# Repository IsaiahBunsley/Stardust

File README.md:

# Stardust
Harmonic gear driven equatorial mount for astrophotography.

GOALS:
 - Achieve sub arcsecond prescision
 - Make a sleek and nice-to-view body assembly
 - Use as few pre-made assemblies as possible
 - Ample wieght capacity ( >10 lbs, ideally >20 lbs )
 - Ease of use/control using pre-developed software such as PHD2, OnStep, etc...
 - Design a PCB to house stepper controllers, microcrontroller, WiFi, etc..
 - Efficient homing process
 - Create a product that is not only good-looking but easy to use and enjoy

NOTES:
V1 Is way to large and clunky

Using a 100:1 harmonic and a ~3.33:1 pulley system we can achieve sub arcsecond tracking using 256 microstepping and approx 20 arcsecond tracking with no microstepping. UPDATE: Using a 0.9deg stepper 10 arcsecond (per step)
can be had. A 0.9deg stepper with 1/16 microstepping will give us 0.6 arcseconds per step. This will have to be used to meet design requiremetns as well as to avoid microstepping as it can lead to error.

M3 bolts were used on bolting the body together. If this does not prove to be rigid enough more bolts can be added or a redesign including angle brackets will be needed.

Clearances with the stepper motors are extremely tight. If NEMA 17 motors will not work it would be OK to swap the DEC axis for a smaller NEMA 14 stepper.

Product IDs for the gears are given but expensive. If suitable replacements with similar specs can be found it would be OK to swap. Same with belts. The only issue would be lack of 
quality control from other sources (Amazon...). Cheaping out on a $20 belt would introduce backlash and tracking errors to the ~$1000 harmonic drives.

The angle brackets used to mount the steppers are called out as 6061 alum alloy but could possibly be 3d printed or bought from Mcmaster Carr if a similar design was found.

A redesign of the tangent mount is needed. This tangent mount is made by William Optics and could be fitted into the design for $250: https://williamoptics.com/products/wo-vixen-style-latitude-base-mount?srsltid=AfmBOoq2dK0res2H1lodv_DhOAtTPYLHiSqc_pLKRGRtTDOESbJT08JW

After looking through the new AM5N's product specs the following seems true:
reduction ratio: 300:1 
         This means that they are using a 100:1 HD paired with a 3:1 belt. With this setup they are claiming a arcsec/step of 0.17. This means that they are using stepper microstepping of 1/64 (0.9 / 300 / 64 = deg -> 0.1687 arcseconds) (also assuming 0.9deg steppers).
There is also a claimed "high payload" mode. I believe that this "mode" simply changes the microstepping value to something more reasonable such as 1/16. This will increase the availiable current per step and thus give more reliable tracking (less periodic error) where more current per step is needed (higher payloads).

DESIGN IDEAS:
For implementing a homing process - Use a arm that mounts to the main axis (axe-eees) that goes down the length of the HD and will pass over some sort of magnetic sensor or inductive position
sensor. This will allow the motors to spin the HD until a sensor detects an object meaning the output shaft of the HD is in the correct location.

Add an encoder and brake to the stepper shaft. 

Allow for EQ mode OR an alt/az mode (by removing the tangent assembly).

INSPIRATION:
Alkaid by JZ - https://github.com/alanzjl/AlkaidMount
ZWO AM5 - https://www.highpointscientific.com/zwo-am5n-harmonic-drive-equatorial-mount-with-tripod
William Optics Latitude Base - https://williamoptics.com/products/wo-vixen-style-latitude-base-mount?srsltid=AfmBOoq2dK0res2H1lodv_DhOAtTPYLHiSqc_pLKRGRtTDOESbJT08JW

0.9 Stepper - https://www.moonsindustries.com/p/nema-17-high-precision-hybrid-stepper-motors/ms17ha4p4040-000004611110015909
ONSTEP      - https://onstep.groups.io/g/main/wiki/4414

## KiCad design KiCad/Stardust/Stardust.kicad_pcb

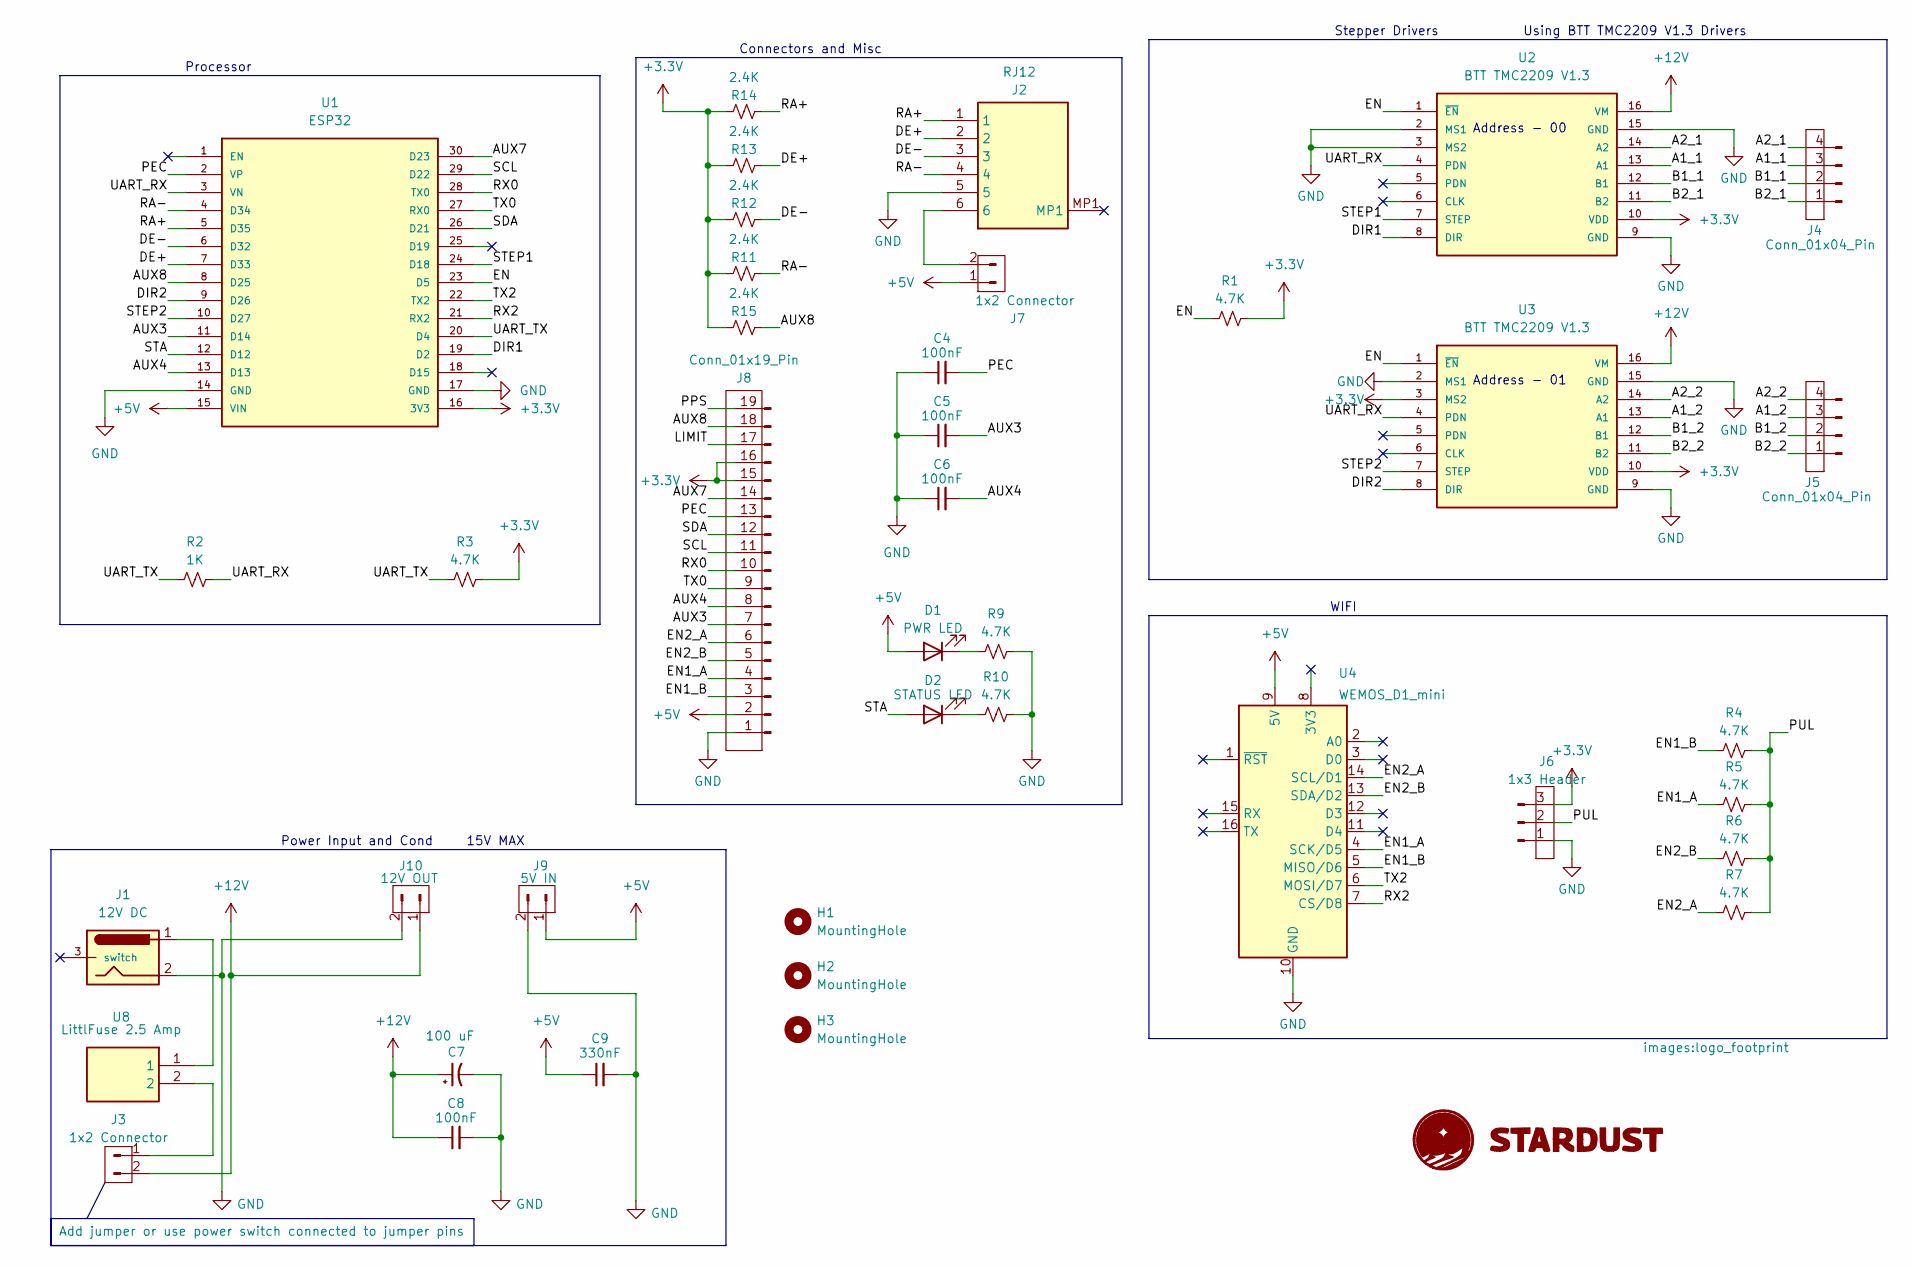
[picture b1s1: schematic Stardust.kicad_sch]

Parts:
C4, C5, C6, C8: 100nF; C_0805_2012Metric_Pad1.18x1.45mm_HandSolder; Mouser PN 581-KAM21BR71H104JT
C7: 100 uF; 100uFElectrolyticCap_CAPAE830X1080N; Mouser PN 647-GXC1V101MCQ1GS
C9: 330nF; C_1206_3216Metric_Pad1.33x1.80mm_HandSolder; Mouser PN 581-KAM31NR81H334KU
D1: PWR LED; LED_0603_1608Metric_Pad1.05x0.95mm_HandSolder
D2: STATUS LED; LED_0603_1608Metric_Pad1.05x0.95mm_HandSolder
G1: LOGO; logo_footprint
H1, H2, H3: MountingHole; MountingHole_3.2mm_M3
J1: 12V DC; DC_PowerConn_694108402002
J2: RJ12; RJ12_855135114; Mouser Part Number 538-85513-5002
J3, J7: 1x2 Connector; PinHeader_1x02_P2.54mm_Vertical
J4, J5: Conn_01x04_Pin; PinHeader_1x04_P2.54mm_Vertical
J6: 1x3 Header; PinHeader_1x03_P2.54mm_Vertical
J8: Conn_01x19_Pin; PinHeader_1x19_P2.54mm_Vertical
J9: 5V IN; PinHeader_1x02_P2.54mm_Vertical
J10: 12V OUT; PinHeader_1x02_P2.54mm_Vertical
R1, R3, R4, R5, R6, R7, R9, R10: 4.7K; R_0805_2012Metric_Pad1.20x1.40mm_HandSolder
R2: 1K; R_0805_2012Metric_Pad1.20x1.40mm_HandSolder
R11, R12, R13, R14, R15: 2.4K; R_0805_2012Metric_Pad1.20x1.40mm_HandSolder
U1: ESP32; MODULE_ESP32-DEVKITC
U2, U3: BTT TMC2209 V1.3; MODULE_TMC2209_SILENTSTEPSTICK
U4: WEMOS_D1_mini; WEMOS_D1_mini_light
U8: LittlFuse 2.5 Amp; FuseHolder_RHDR2W53P0X508_1X2; Mouser Part Number 576-56200001009

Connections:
+3.3V: J6.3, J8.15, J8.16, R1.2, R3.2, R11.2, R12.2, R13.2, R14.2, R15.2, U1.16 (3V3), U2.10 (VDD), U3.3 (MS2), U3.10 (VDD)
+5V: C9.1, D1.2 (A), J7.1, J8.2, J9.1, U1.15 (VIN), U4.9 (5V)
+12V: C7.1, C8.1, J3.2, J10.1, U2.16 (VM), U3.16 (VM)
/A1_1: J4.3, U2.13 (A1)
/A1_2: J5.3, U3.13 (A1)
/A2_1: J4.4, U2.14 (A2)
/A2_2: J5.4, U3.14 (A2)
/AUX3: C5.2, J8.7, U1.11 (D14)
/AUX4: C6.2, J8.8, U1.13 (D13)
/AUX7: J8.14, U1.30 (D23)
/AUX8: J8.18, R15.1, U1.8 (D25)
/B1_1: J4.2, U2.12 (B1)
/B1_2: J5.2, U3.12 (B1)
/B2_1: J4.1, U2.11 (B2)
/B2_2: J5.1, U3.11 (B2)
/DE+: J2.2, R13.1, U1.7 (D33)
/DE-: J2.3, R12.1, U1.6 (D32)
/DIR1: U1.19 (D2), U2.8 (DIR)
/DIR2: U1.9 (D26), U3.8 (DIR)
/EN: R1.1, U1.23 (D5), U2.1 (~EN), U3.1 (~EN)
/EN1_A: J8.4, R5.1, U4.4 (SCK/D5)
/EN1_B: J8.3, R4.1, U4.5 (MISO/D6)
/EN2_A: J8.6, R7.1, U4.14 (SCL/D1)
/EN2_B: J8.5, R6.1, U4.13 (SDA/D2)
/LIMIT: J8.17
/PEC: C4.2, J8.13, U1.2 (VP)
/PPS: J8.19
/PUL: J6.2, R4.2, R5.2, R6.2, R7.2
/RA+: J2.1, R14.1, U1.5 (D35)
/RA-: J2.4, R11.1, U1.4 (D34)
/RX0: J8.10, U1.28 (TX0)
/RX2: U1.21 (RX2), U4.7 (CS/D8)
/SCL: J8.11, U1.29 (D22)
/SDA: J8.12, U1.26 (D21)
/STA: D2.2 (A), U1.12 (D12)
/STEP1: U1.24 (D18), U2.7 (STEP)
/STEP2: U1.10 (D27), U3.7 (STEP)
/TX0: J8.9, U1.27 (RX0)
/TX2: U1.22 (TX2), U4.6 (MOSI/D7)
/UART_RX: R2.2, U1.3 (VN), U2.4 (PDN), U3.4 (PDN)
/UART_TX: R2.1, R3.1, U1.20 (D4)
GND: C4.1, C5.1, C6.1, C7.2, C8.2, C9.2, J1.2, J2.5, J6.1, J8.1, J9.2, J10.2, R9.2, R10.2, U1.14 (GND), U1.17 (GND), U2.2 (MS1), U2.3 (MS2), U2.9 (GND), U2.15 (GND), U3.2 (MS1), U3.9 (GND), U3.15 (GND), U4.10 (GND)
unnamed: D1.1 (K), R9.1
unnamed: D2.1 (K), R10.1
unnamed: J1.1, U8.1
unnamed: J3.1, U8.2
unnamed: J2.6, J7.2

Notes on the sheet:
Processor
Connectors and Misc
Using BTT TMC2209 V1.3 Drivers
WIFI
15V MAX
Stepper Drivers
Address - 01
Power Input and Cond
Address - 00

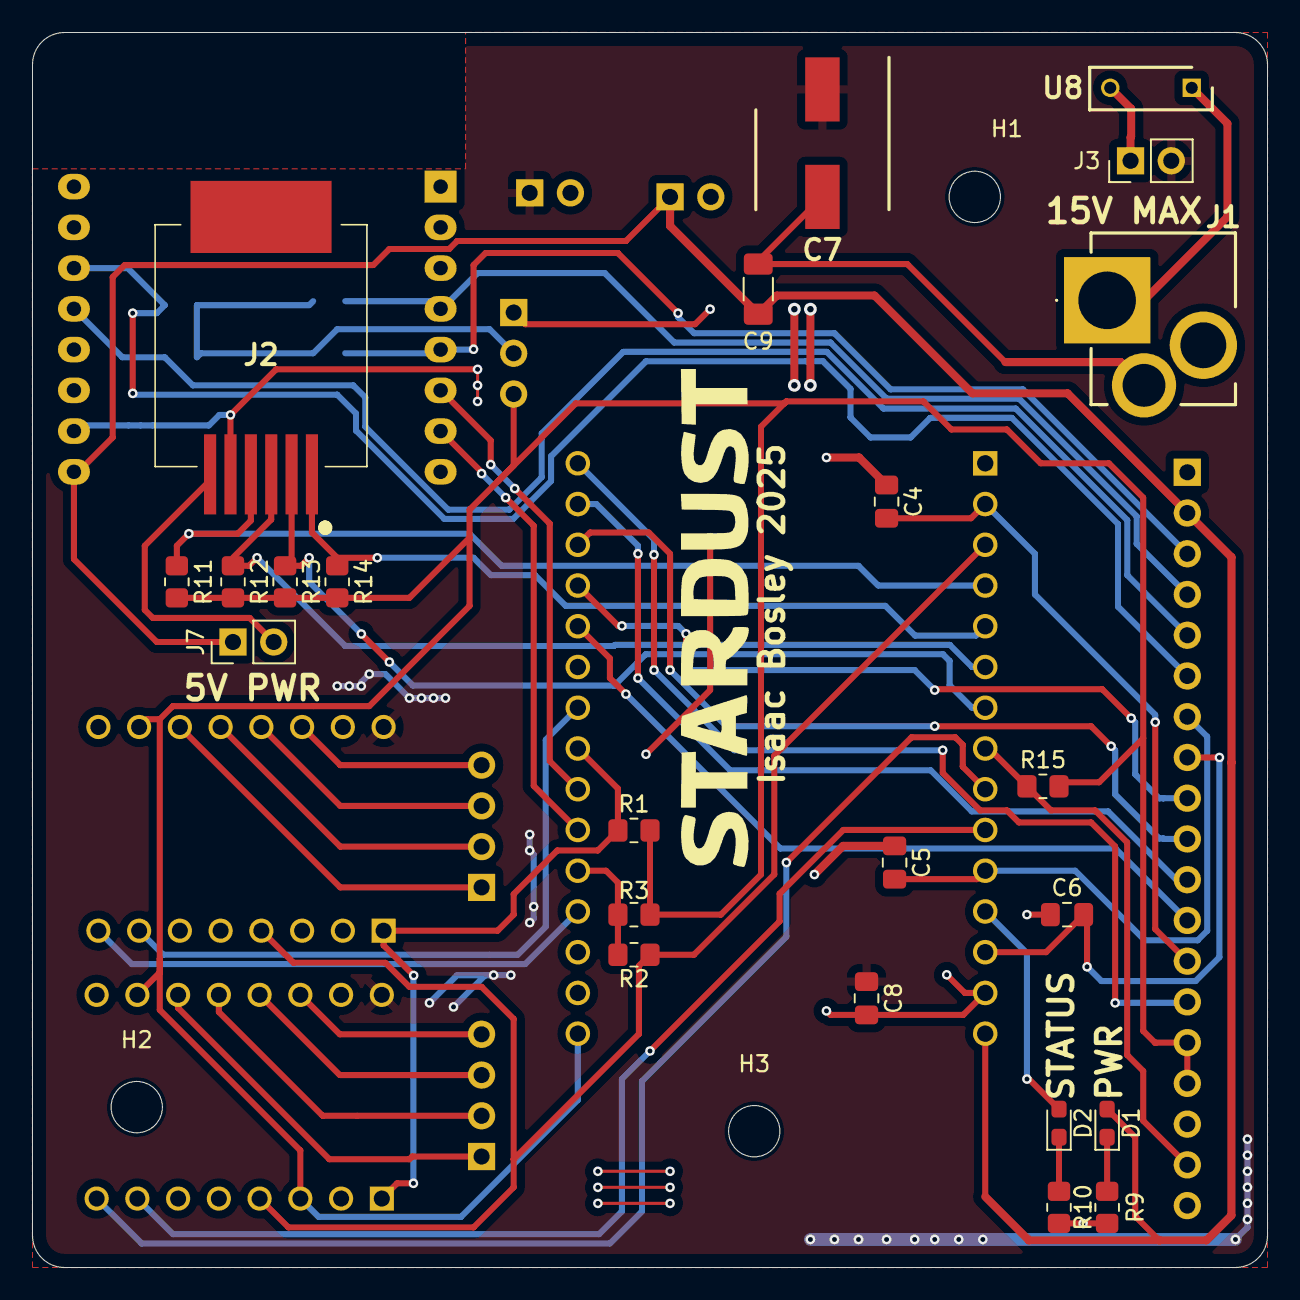
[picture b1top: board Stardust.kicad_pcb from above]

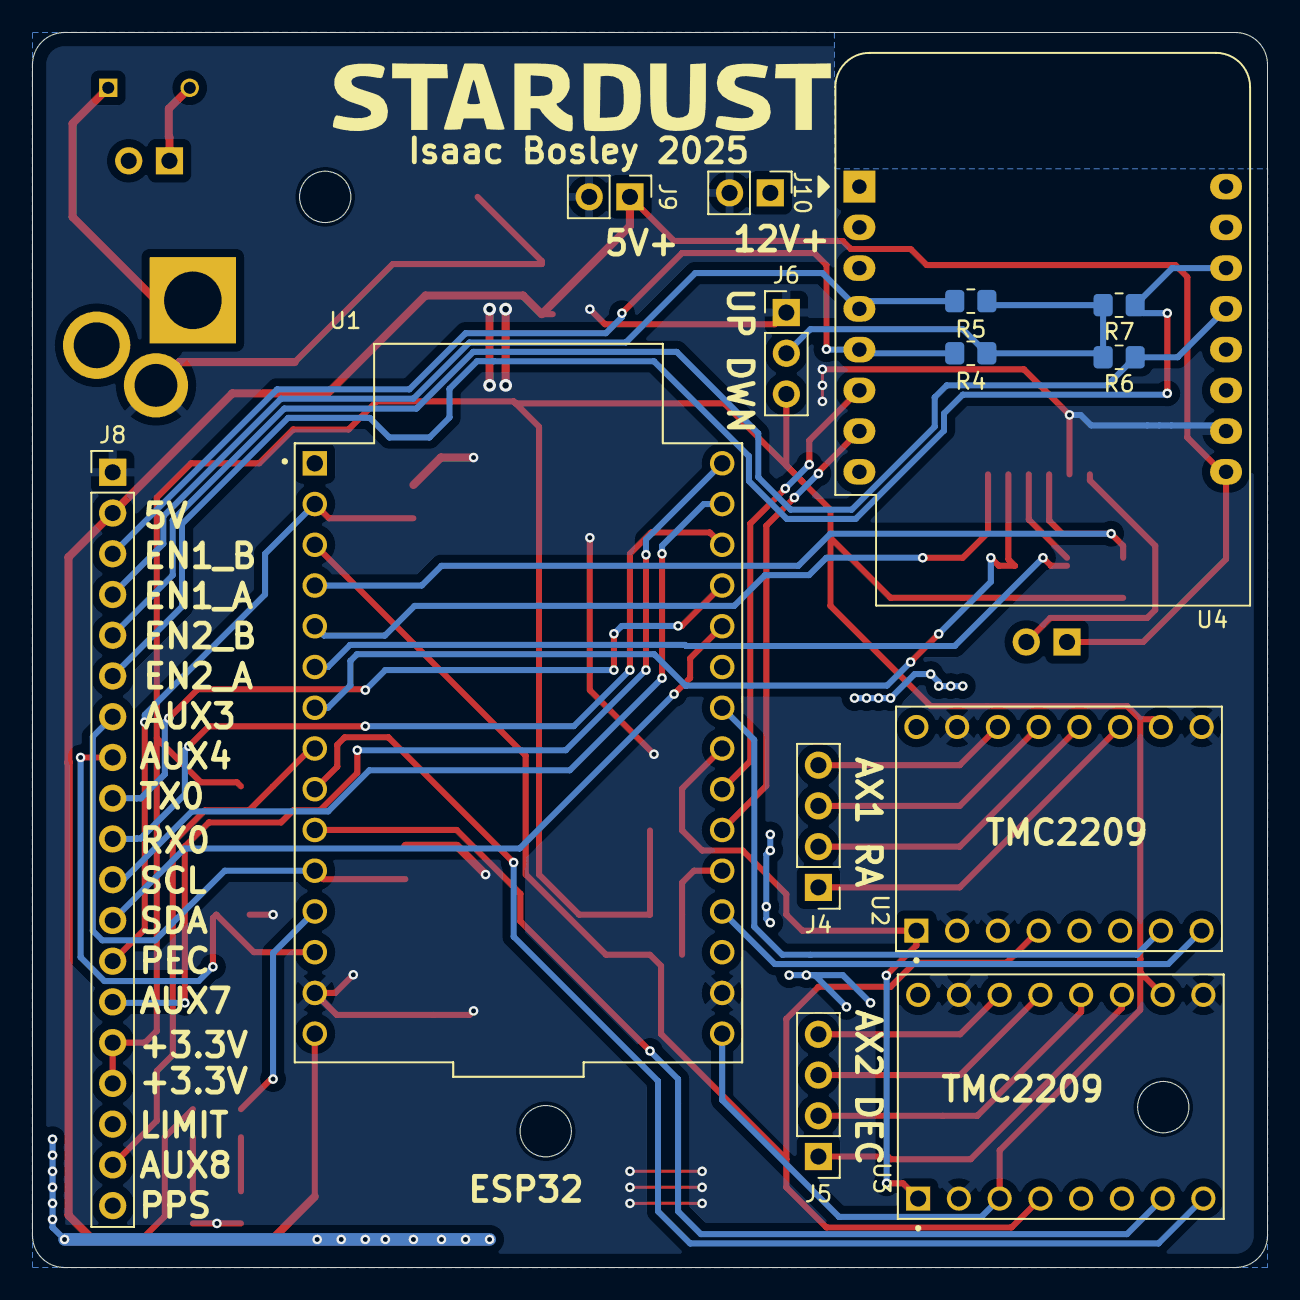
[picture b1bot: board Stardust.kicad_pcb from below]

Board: 2 copper layers, 77.0 x 77.0 mm, 42 parts (15 on the bottom side), 45 nets.

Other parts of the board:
G1#2: LOGO; logo_footprint

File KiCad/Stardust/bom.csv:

"Id";"Designator";"Footprint";"Quantity";"Designation";"Supplier and ref";
1;"C6,C5,C8,C4";"C_2220_5750Metric_Pad1.97x5.40mm_HandSolder";4;"100nF";;;
2;"R1,R3,R9,R10,R6,R5,R4,R7";"R_0805_2012Metric_Pad1.20x1.40mm_HandSolder";8;"4.7K";;;
3;"D2";"LED_0603_1608Metric_Pad1.05x0.95mm_HandSolder";1;"STATUS LED";;;
4;"J7,J3";"PinHeader_1x02_P2.54mm_Vertical";2;"1x2 Connector";;;
5;"J2";"RJ12_855135114";1;"RJ12";;;
6;"R14,R15,R13,R12,R11";"R_0805_2012Metric_Pad1.20x1.40mm_HandSolder";5;"2.4K";;;
7;"U8";"FuseHolder_RHDR2W53P0X508_1X2";1;"LittlFuse 2.5 Amp";;;
8;"G1,G1";"logo_footprint";2;"LOGO";;;
9;"C7";"100uFElectrolyticCap_CAPAE830X1080N";1;"100 uF";;;
10;"U7";"5VREG_SOT230P700X180-4N";1;"Regulator - 5V 1A";;;
11;"C2,C1";"10uFElectrolyticCap_CAPAE660X550N";2;"10 uF";;;
12;"D1";"LED_0603_1608Metric_Pad1.05x0.95mm_HandSolder";1;"PWR LED";;;
13;"C3";"C_0603_1608Metric_Pad1.08x0.95mm_HandSolder";1;"10uF";;;
14;"C9";"C_1206_3216Metric_Pad1.33x1.80mm_HandSolder";1;"330nF";;;
15;"R2";"R_0805_2012Metric_Pad1.20x1.40mm_HandSolder";1;"1K";;;
16;"J1";"DC_PowerConn_694108402002";1;"12V DC";;;
17;"U2,U3";"MODULE_TMC2209_SILENTSTEPSTICK";2;"BTT TMC2209 V1.3";;;
18;"U1";"MODULE_ESP32-DEVKITC";1;"ESP32";;;
19;"J5,J4";"PinHeader_1x04_P2.54mm_Vertical";2;"Conn_01x04_Pin";;;
20;"J6";"PinHeader_1x03_P2.54mm_Vertical";1;"1x3 Header";;;
21;"J8";"PinHeader_1x19_P2.54mm_Vertical";1;"Conn_01x19_Pin";;;
22;"U4";"WEMOS_D1_mini_light";1;"WEMOS_D1_mini";;;

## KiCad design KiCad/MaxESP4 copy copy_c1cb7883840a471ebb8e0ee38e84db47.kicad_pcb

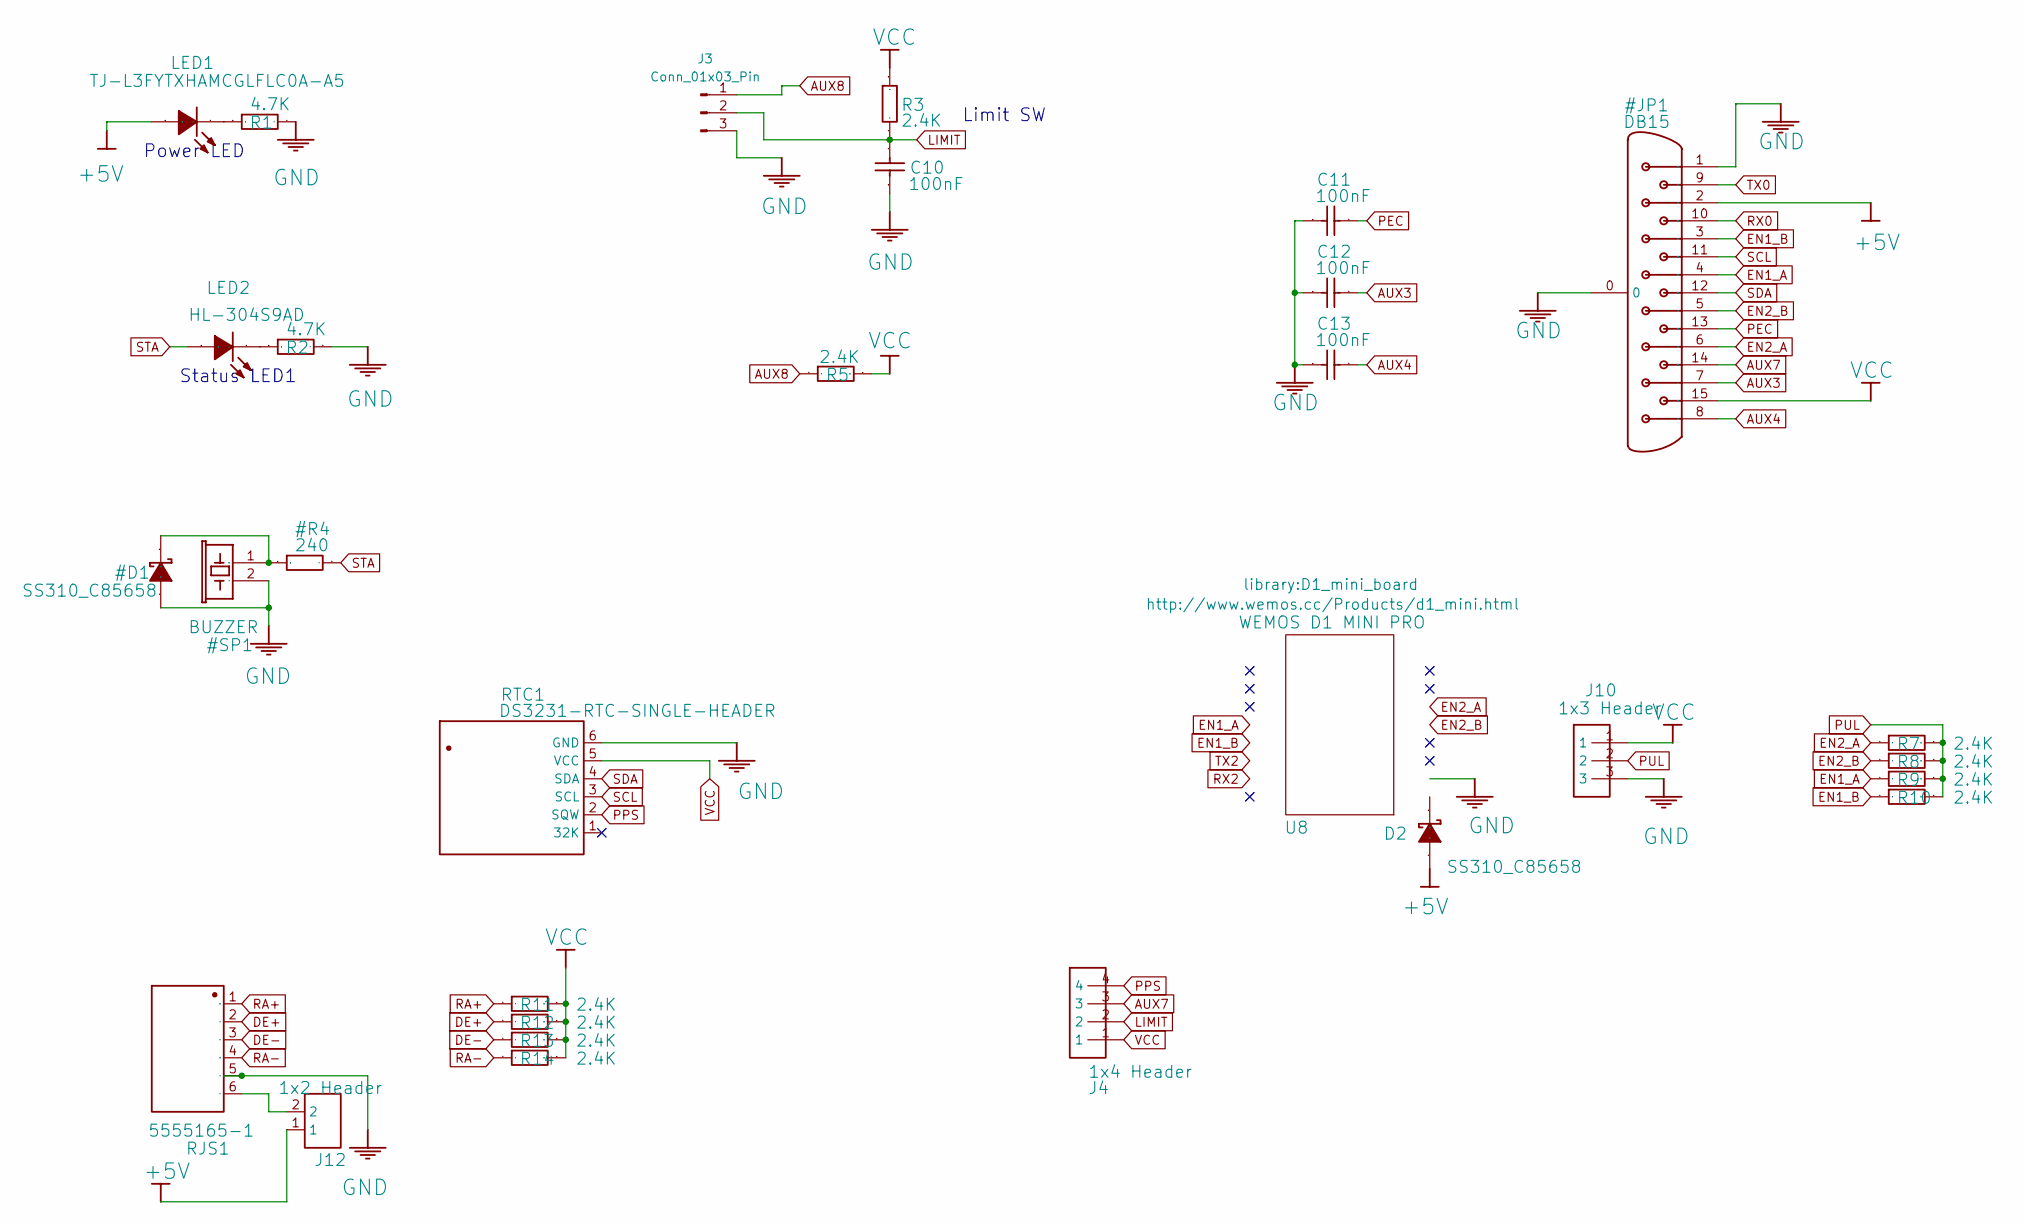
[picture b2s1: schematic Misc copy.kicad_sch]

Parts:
C10, C11, C12, C13: 100nF; 0.1uF_CAPC2012X94N
D2: SS310_C85658; Schottky_SODFL5336X130N
J3: Conn_01x03_Pin; PinHeader_1x03_P2.54mm_Vertical
J4: 1x4 Header; PinHeader_1x04_P2.54mm_Vertical
J10: 1x3 Header; PinHeader_1x03_P2.54mm_Vertical
J12: 1x2 Header; PinHeader_1x02_P2.54mm_Vertical
LED1: TJ-L3FYTXHAMCGLFLC0A-A5; LED_AA1608LZGSK295V
LED2: HL-304S9AD; LED_AA1608LZGSK295V
R1, R2: 4.7K; 4.7K_Resistor_ERA8P
R3, R5, R7, R8, R9, R10, R11, R12, R13, R14: 2.4K; 2.4K_Resistor_ERJUP6
RJS1: 5555165-1
RTC1: DS3231-RTC-SINGLE-HEADER
U8: WEMOS D1 MINI PRO; D1_mini_board

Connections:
AUX8: J3.1, R5.2; also elsewhere on the board
DE+: R12.2, RJS1.2; also elsewhere on the board
DE-: R13.2, RJS1.3; also elsewhere on the board
LIMIT: C10.2, J3.2, J4.2, R3.2
unnamed: D2.1 (K), U8.1 (5V)
unnamed: J12.2, RJS1.6
unnamed: LED1.2 (C), R1.1
unnamed: LED2.2 (C), R2.1
PPS: J4.4, RTC1.2 (SQW)
PUL: J10.2, R7.1, R8.1, R9.1, R10.1
RA+: R11.2, RJS1.1; also elsewhere on the board
RA-: R14.2, RJS1.4; also elsewhere on the board
RX2: U8.15 (D8); also elsewhere on the board
TX2: U8.14 (D7); also elsewhere on the board

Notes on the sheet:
Limit SW
Status LED1
Power LED

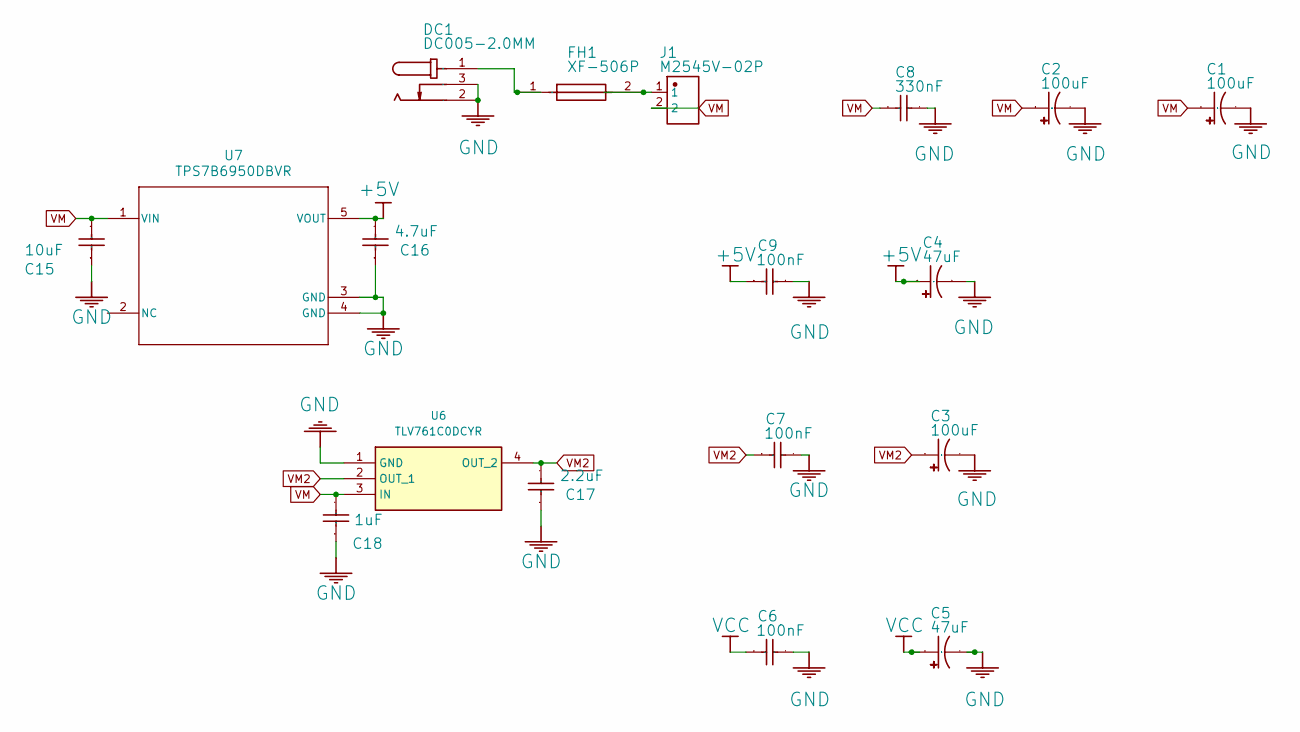
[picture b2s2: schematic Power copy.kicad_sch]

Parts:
C1, C2, C3: 100uF; 47uF_100uF_Capacitor_CAPAE830X1080N
C4, C5: 47uF; 47uF_100uF_Capacitor_CAPAE830X1080N
C6, C7, C9: 100nF; 0.1uF_CAPC2012X94N
C8: 330nF; 0.33uF_Capacitor_CAPC3216X127N
C15: 10uF; 0.1uF_CAPC2012X94N
C16: 4.7uF; 0.1uF_CAPC2012X94N
C17: 2.2uF; 0.1uF_CAPC2012X94N
C18: 1uF; 0.1uF_CAPC2012X94N
DC1: DC005-2.0MM; DC_PowerConn_694108402002
FH1: XF-506P; FuseHolder_RHDR2W53P0X508_1X2_765X255X455P
J1: M2545V-02P; PinHeader_1x02_P2.54mm_Vertical
U6: TLV761C0DCYR; SOT230P700X180-4N; Mouser Part Number 595-TLV761C0DCYR
U7: TPS7B6950DBVR; DBV0005A_N

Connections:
unnamed: DC1.1, FH1.1
unnamed: FH1.2, J1.1
VM: C1.1, C2.1, C8.1, C15.2, C18.2, J1.2, U6.3 (IN), U7.1 (VIN); also elsewhere on the board

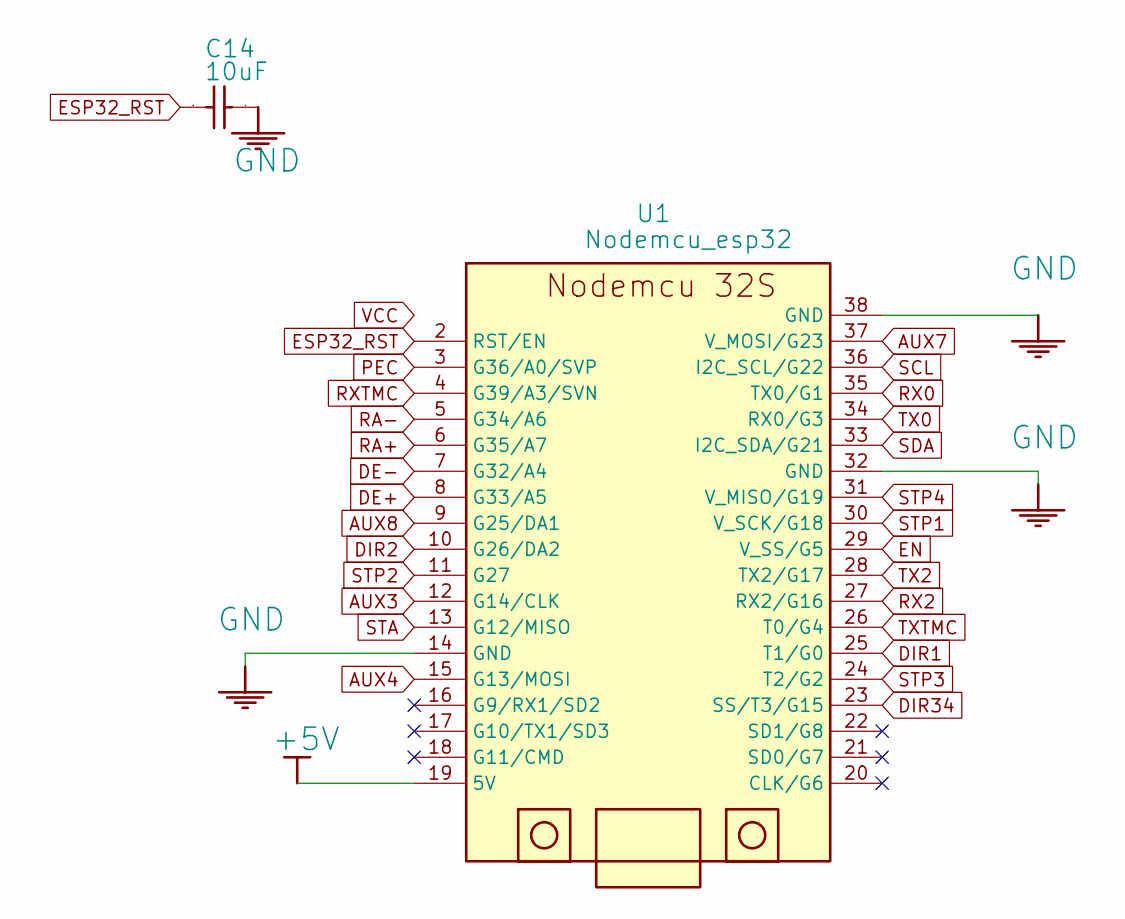
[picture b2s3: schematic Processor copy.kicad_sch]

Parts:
C14: 10uF; 10uF_Capacitor_CAPC3216X190N
U1: Nodemcu_esp32; MODULE_ESP32-DEVKITC

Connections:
AUX8: U1.9 (G25/DA1); also elsewhere on the board
DE+: U1.8 (G33/A5); also elsewhere on the board
DE-: U1.7 (G32/A4); also elsewhere on the board
DIR1: U1.25 (T1/G0); also elsewhere on the board
DIR2: U1.10 (G26/DA2); also elsewhere on the board
DIR34: U1.23 (SS/T3/G15)
ESP32_RST: C14.1, U1.2 (RST/EN)
RA+: U1.6 (G35/A7); also elsewhere on the board
RA-: U1.5 (G34/A6); also elsewhere on the board
RX0: U1.35 (TX0/G1)
RX2: U1.27 (RX2/G16); also elsewhere on the board
STP1: U1.30 (V_SCK/G18); also elsewhere on the board
STP2: U1.11 (G27); also elsewhere on the board
STP3: U1.24 (T2/G2)
STP4: U1.31 (V_MISO/G19)
TX0: U1.34 (RX0/G3)
TX2: U1.28 (TX2/G17); also elsewhere on the board
TXTMC: U1.26 (T0/G4); also elsewhere on the board

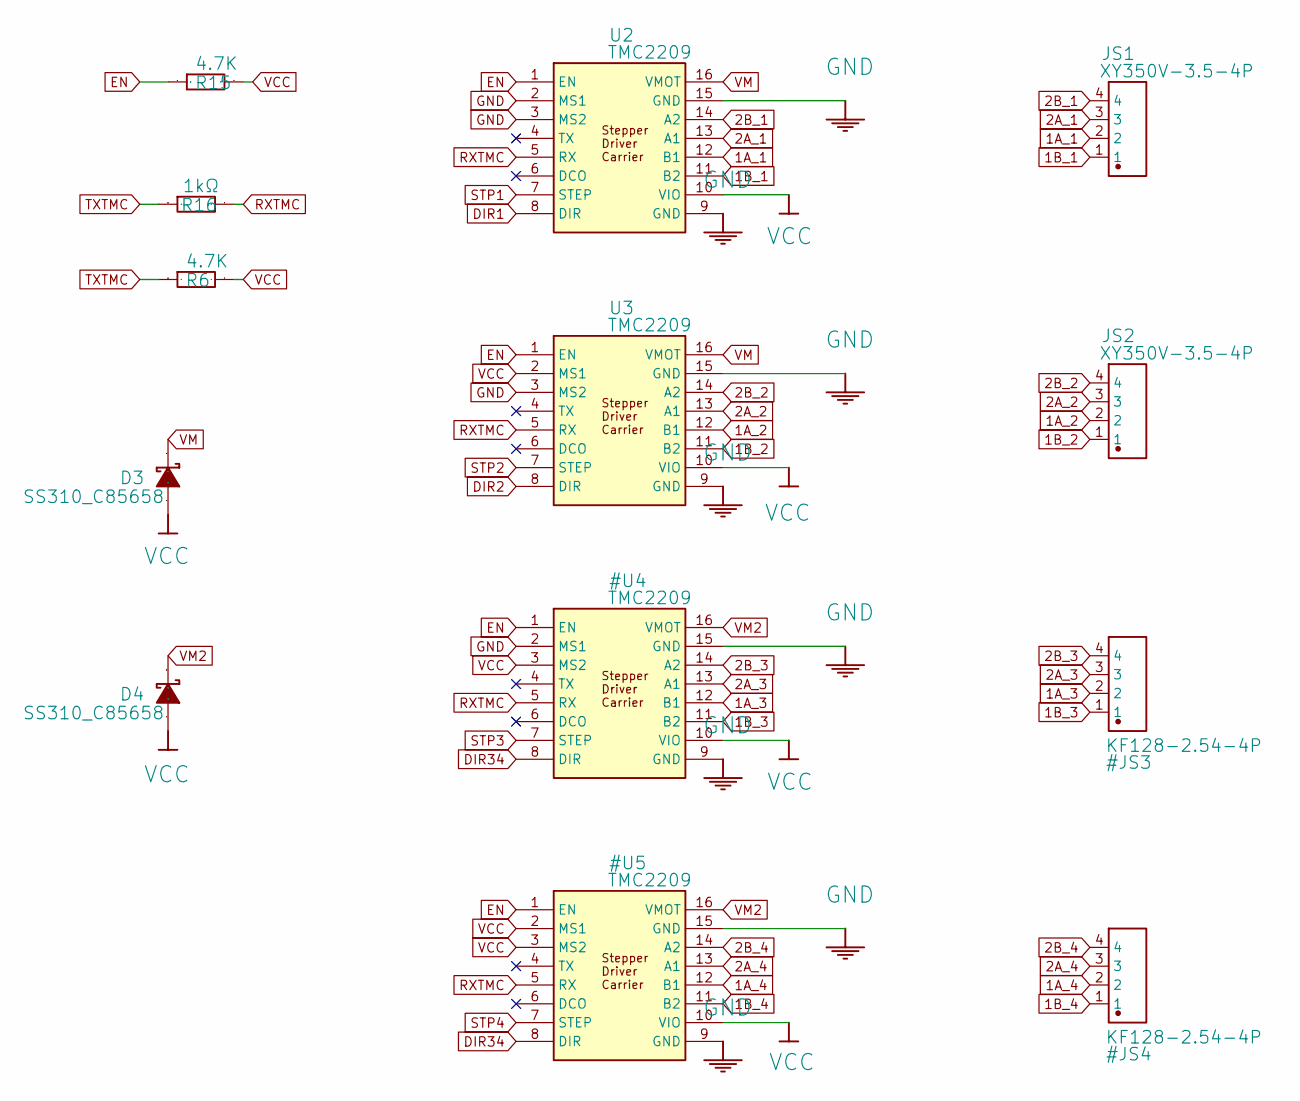
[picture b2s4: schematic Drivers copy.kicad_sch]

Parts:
D3, D4: SS310_C85658; Schottky_SODFL5336X130N
JS1, JS2: XY350V-3.5-4P; PinHeader_1x04_P2.54mm_Vertical
R6, R15: 4.7K; 4.7K_Resistor_ERA8P
R16: 1kΩ; 1k_Resistor_RESC3216X70N
U2, U3: TMC2209; MODULE_TMC2209_SILENTSTEPSTICK

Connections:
1A_1: JS1.2, U2.12 (B1)
1A_2: JS2.2, U3.12 (B1)
1B_1: JS1.1, U2.11 (B2)
1B_2: JS2.1, U3.11 (B2)
2A_1: JS1.3, U2.13 (A1)
2A_2: JS2.3, U3.13 (A1)
2B_1: JS1.4, U2.14 (A2)
2B_2: JS2.4, U3.14 (A2)
DIR1: U2.8 (DIR); also elsewhere on the board
DIR2: U3.8 (DIR); also elsewhere on the board
STP1: U2.7 (STEP); also elsewhere on the board
STP2: U3.7 (STEP); also elsewhere on the board
TXTMC: R6.1, R16.1; also elsewhere on the board
VM: D3.1 (K), U2.16 (VMOT), U3.16 (VMOT); also elsewhere on the board

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
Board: 2 copper layers, 54 parts (0 on the bottom side), 47 nets, no tracks yet.

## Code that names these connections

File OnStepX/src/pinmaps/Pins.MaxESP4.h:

// -------------------------------------------------------------------------------------------------
// Pin map for OnStep MaxESP4 (ESP32S)
#pragma once

#if defined(ESP32)

// Serial0: RX Pin GPIO3, TX Pin GPIO1 (to USB serial adapter)
// Serial1: RX1 Pin GPIO10, TX1 Pin GPIO9 (on SPI Flash pins, must be moved to be used)
// Serial2: RX2 Pin GPIO16, TX2 Pin GPIO17

#if SERIAL_A_BAUD_DEFAULT != OFF
  #define SERIAL_A              Serial
#endif
#if SERIAL_B_BAUD_DEFAULT != OFF
  #define SERIAL_B              Serial2
#endif

// Use the following settings for any TMC UART driver (TMC2209) that may be present
#if defined(STEP_DIR_TMC_UART_PRESENT) || defined(SERVO_TMC2209_PRESENT)
  #define SERIAL_TMC_HARDWARE_UART
  #define SERIAL_TMC            Serial1          // Use a single hardware serial port to up to four drivers
  #define SERIAL_TMC_BAUD       460800           // Baud rate
  #define SERIAL_TMC_RX         39               // Recieving data
  #define SERIAL_TMC_TX         4                // Transmit data
  #define SERIAL_TMC_ADDRESS_MAP(x) ((x==1)?2 : x) // Axis1(0) is 0, Axis2(1) is 1, Axis3(2) is 2, Axis4(3) is 3, Axis5(4) is 2
#endif

// Specify the ESP32 I2C pins
#define I2C_SDA_PIN             21
#define I2C_SCL_PIN             22

// The multi-purpose pins (Aux3..Aux8 can be analog pwm/dac if supported)
#define AUX2_PIN                39               // M3 pin TMC UART RX
#define AUX3_PIN                14               // Home SW for Axis1
#define AUX4_PIN                13               // Home SW for Axis2
#define AUX5_PIN                1                // TX0 main USB, etc.
#define AUX6_PIN                3                // RX0 main USB, etc.
#define AUX7_PIN                23               // Limit SW, PPS, etc.
#define AUX8_PIN                25               // 1-Wire, Status LED, Reticle LED, Tone, etc.

// Misc. pins
#ifndef ONE_WIRE_PIN
  #define ONE_WIRE_PIN          AUX8_PIN         // Default Pin for OneWire bus
#endif

// The PEC index sense is a logic level input, resets the PEC index on rising edge then waits for 60 seconds before allowing another reset
#ifndef PEC_SENSE_PIN
  #define PEC_SENSE_PIN         36               // [input only 36] PEC Sense, analog (A0) or digital (GPIO36)
#endif

// The status LED w/ 4.7k resistor in series to limit the current to the LED
#ifdef STATUS_LED_ON_STATE
  #undef STATUS_LED_ON_STATE
#endif
#define STATUS_LED_ON_STATE HIGH
#ifndef STATUS_LED_PIN
  #define STATUS_LED_PIN        12               // Default LED Anode (+)
#endif
#ifdef MOUNT_LED_ON_STATE
  #undef MOUNT_LED_ON_STATE
#endif
#define MOUNT_LED_ON_STATE      HIGH
#define MOUNT_LED_PIN           STATUS_LED_PIN   // Default LED Anode (+)
#ifndef RETICLE_LED_PIN
  #define RETICLE_LED_PIN       AUX8_PIN         // Default LED Cathode (-)
#endif

// For a piezo buzzer
#ifndef STATUS_BUZZER_PIN
  #define STATUS_BUZZER_PIN     12               // [must be low at boot 12] Tone
#endif

// The PPS pin is a 3.3V logic input, OnStep measures time between rising edges and adjusts the internal sidereal clock frequency
#ifndef PPS_SENSE_PIN
  #define PPS_SENSE_PIN         AUX7_PIN         // PPS time source, GPS for example
#endif

// The limit switch sense is a logic level input normally pull high (2k resistor,) shorted to ground it stops gotos/tracking
#ifndef LIMIT_SENSE_PIN
  #define LIMIT_SENSE_PIN       AUX7_PIN
#endif

#define SHARED_DIRECTION_PINS                    // Hint that the direction pins are shared
#define SHARED_ENABLE_PIN       5                // Hint that the enable pins are shared

// Axis1 RA/Azm step/dir driver
#define AXIS1_ENABLE_PIN        SHARED           // Enable pin control
#define AXIS1_M0_PIN            OFF              // hardwired for TMC UART address 0
#define AXIS1_M1_PIN            OFF              // hardwired for TMC UART address 0
#define AXIS1_M2_PIN            OFF              // UART TX
#define AXIS1_M3_PIN            OFF              // UART RX
#define AXIS1_STEP_PIN          18
#define AXIS1_DIR_PIN           2                // [must be high at boot 0]
#ifndef AXIS1_SENSE_HOME_PIN
  #define AXIS1_SENSE_HOME_PIN  AUX3_PIN
#endif

// Axis2 Dec/Alt step/dir driver
#define AXIS2_ENABLE_PIN        SHARED
#define AXIS2_M0_PIN            OFF              // hardwired for TMC UART address 1
#define AXIS2_M1_PIN            OFF              // hardwired for TMC UART address 1
#define AXIS2_M2_PIN            OFF              // N/C
#define AXIS2_M3_PIN            OFF              // UART RX
#define AXIS2_STEP_PIN          27
#define AXIS2_DIR_PIN           26
#ifndef AXIS2_SENSE_HOME_PIN
  #define AXIS2_SENSE_HOME_PIN  AUX4_PIN
#endif
#ifndef AXIS2_ENCODER_B_PIN
  #define AXIS2_ENCODER_B_PIN   AUX2_PIN
#endif

// For rotator stepper driver
#define AXIS3_ENABLE_PIN        SHARED
#define AXIS3_M0_PIN            OFF              // hardwired for TMC UART address 2
#define AXIS3_M1_PIN            OFF              // hardwired for TMC UART address 2
#define AXIS3_M2_PIN            OFF              // N/C
#define AXIS3_M3_PIN            OFF              // UART RX
#define AXIS3_STEP_PIN          2                // [must be low at boot 2]
#define AXIS3_DIR_PIN           15

// For focuser1 stepper driver
#define AXIS4_ENABLE_PIN        SHARED
#define AXIS4_M0_PIN            OFF              // hardwired for TMC UART address 3
#define AXIS4_M1_PIN            OFF              // hardwired for TMC UART address 3
#define AXIS4_M2_PIN            OFF              // N/C
#define AXIS4_M3_PIN            OFF              // UART RX
#define AXIS4_STEP_PIN          19
#define AXIS4_DIR_PIN           15

// For focuser2 stepper driver
#define AXIS5_ENABLE_PIN        SHARED
#define AXIS5_M0_PIN            OFF              // hardwired for TMC UART address 2
#define AXIS5_M1_PIN            OFF              // hardwired for TMC UART address 2
#define AXIS5_M2_PIN            OFF              // N/C
#define AXIS5_M3_PIN            OFF              // UART RX
#define AXIS5_STEP_PIN          2
#define AXIS5_DIR_PIN           15

// ST4 interface
#define ST4_RA_W_PIN            34               // [input only 34] ST4 RA- West
#define ST4_DEC_S_PIN           32               // ST4 DE- South
#define ST4_DEC_N_PIN           33               // ST4 DE+ North
#define ST4_RA_E_PIN            35               // [input only 35] ST4 RA+ East

#else
#error "Wrong processor for this configuration!"

#endif

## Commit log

2024-03-21 Initial
2024-03-21 Added tangent and dovetail models made by JZ (Alkaid)
2024-03-21 Revised both axis mounts to be smaller and more sleek looking. Also decided on using M3 to mount entire thing together (may upsize later)
2024-03-21 Added blanks for top and computer panels as well as an expense tracker and hours tracker
2024-03-21 Switched top and computer locations around. Also added a M12x1.75 tap hole for a counterweight on back.
2024-03-22 Begun work on stepper mounts and adding in gearing/shafts.
2024-03-22 Added in correct models for gears and mated everything accordingly.
2024-03-22 Changed material to 6061 alum alloy. Cleaned up construction lines.
2024-03-22 Cleanup
2024-03-28 Updated hours
2024-04-02 Updated Excel sheet
2024-04-02 Removed sldwrks files
2024-04-09 Added a electronics mount plate and changes some materials and colors. Also added a HD cover for looks and eventually addding the prox sensor and metal piece.
2024-09-04 Update README.md
    extra notes
2024-09-04 Added .step file for easy viewing of asm
    The .step contains the tangent assembly from Alkaid mount as well as a dovetail from the same project. The final Stardust design will NOT include these models.
2024-09-05 Update README.md
    ideas
2024-11-13 Added nut holes for better bolting
2025-02-18 Added Kicad stuff and updates some of the models.
2025-02-18 More work on sch and board layout
2025-02-19 Finished schematic (V1.0)
2025-02-19 Added parts for everything as well as assigned footprints. Board should be ready to finish
2025-02-20 Finished board design and created gerber files
2025-02-20 Added silkscreen images
2025-02-20 Added 3d model of full board and a bom
2025-02-20 Added bom and replaced expensive cap
2025-02-20 updated bom and cleanup
2025-02-20 Fixed some power plane issues and added mounting holes
2025-03-02 Added software libraries for onstep as well as the configured code required to upload to esp32. Also included some Arduino libraries
2025-03-05 Started revising board. Did stepper drivers and updated some footprints
2025-03-18 updated 3d model. Added new model parts. Updated board and firmware. Everything should be working in this rev
2025-03-18 worked on computer mount model and cover
